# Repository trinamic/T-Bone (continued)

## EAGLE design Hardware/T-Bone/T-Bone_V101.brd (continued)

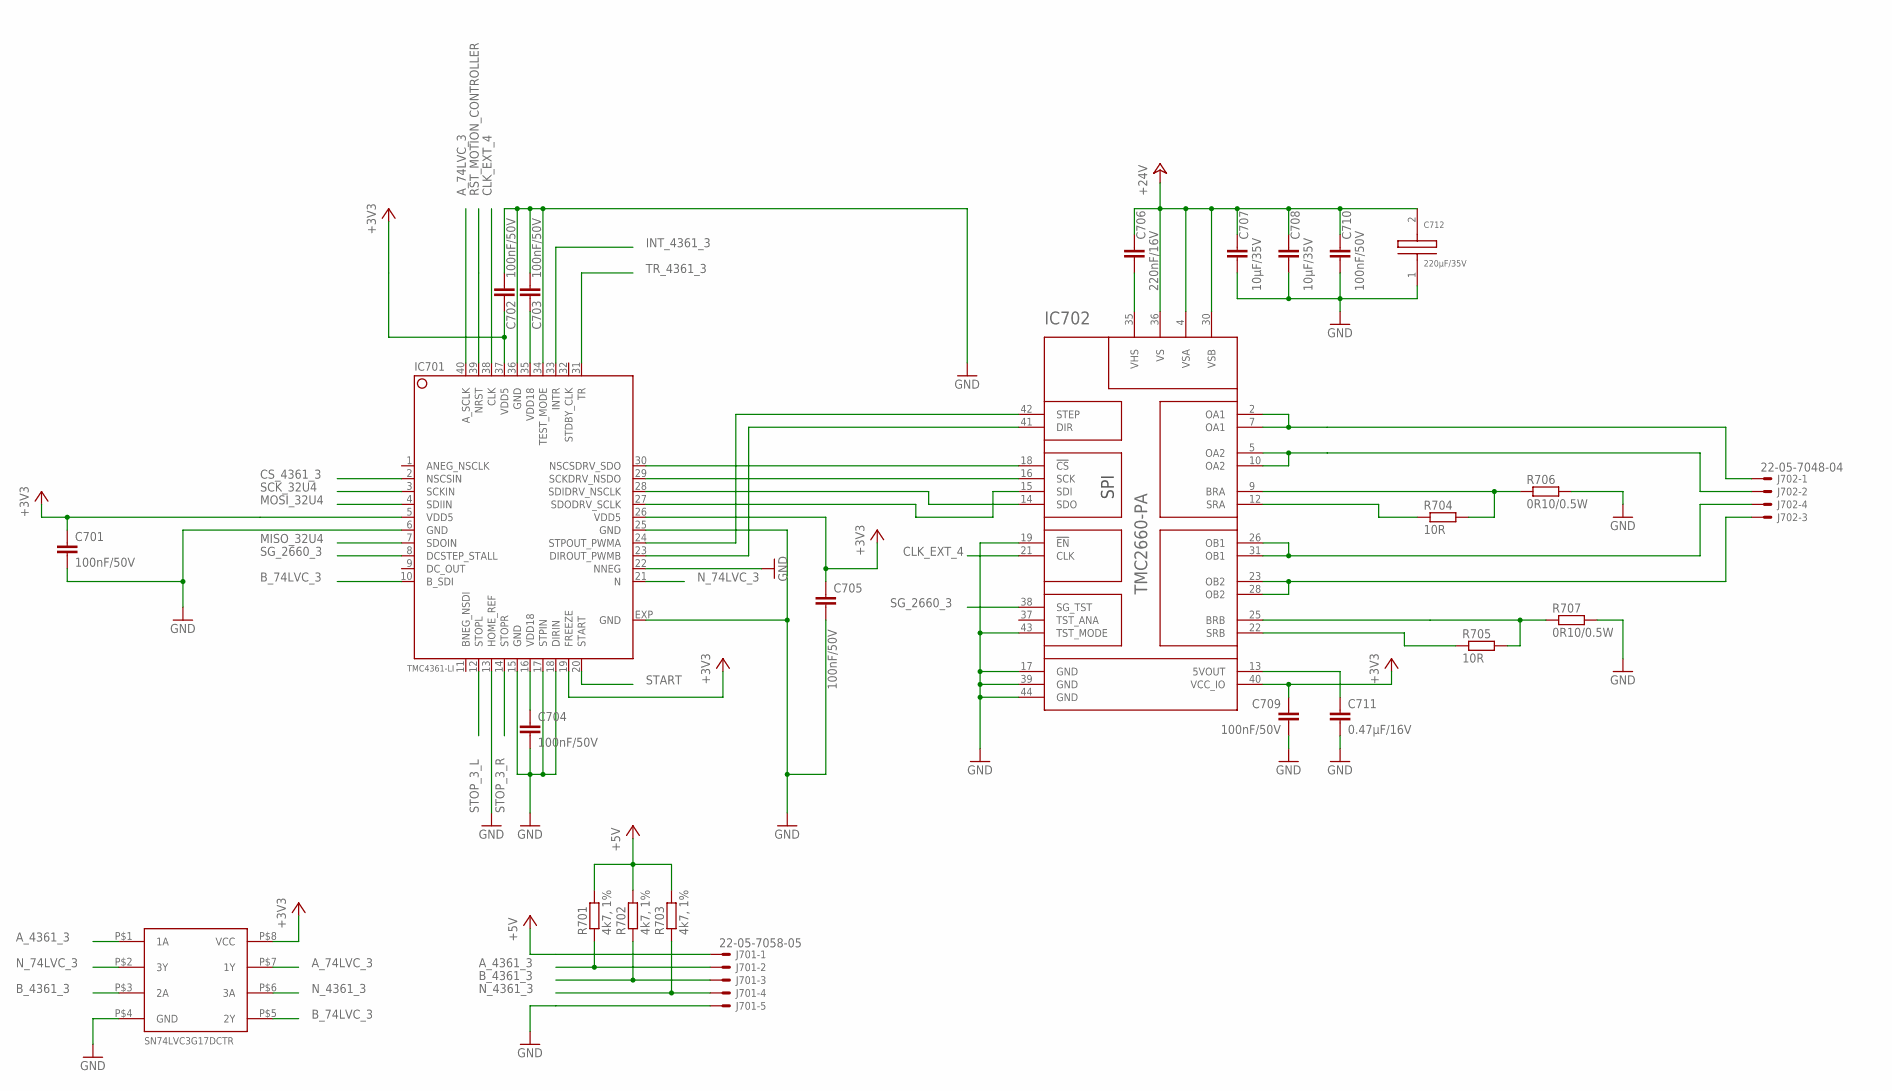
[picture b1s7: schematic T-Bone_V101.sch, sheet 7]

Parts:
C701, C702, C703, C704, C705, C709, C710: 100nF/50V; C0603K
C706: 220nF/16V; C0603K
C707, C708: 10µF/35V; C1210K
C711: 0.47µF/16V; C0603K
C712: 220µF/35V; F
IC701: TMC4361-LI; QFN40L
IC702: TMC2660-PA; PQFP44_WITH_PADS
J701: 22-05-7058-05; 7395-05
J702: 22-05-7048-04; 7395-04
R701, R702, R703: 4k7, 1%; R0603
R704, R705: 10R; R0603
R706, R707: 0R10/0.5W; R1206
U$701: SN74LVC3G17-SM8

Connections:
+3V3: C701.1, C702.2, C705.1, C709.1, IC701.5 (VDD5), IC701.19 (FREEZE), IC701.26 (VDD5), IC701.37 (VDD5), IC702.40 (VCC_IO), U$701.P$8 (VCC); also elsewhere on the board
+5V: J701.1, R701.2, R702.2, R703.2; also elsewhere on the board
+24V: C706.1, C707.1, C708.1, C710.1, C712.2, IC702.4 (VSA), IC702.30 (VSB), IC702.36 (VS); also elsewhere on the board
A_74LVC_3: IC701.40 (A_SCLK), U$701.P$7 (1Y)
A_4361_3: J701.2, R701.1, U$701.P$1 (1A)
B_74LVC_3: IC701.10 (B_SDI), U$701.P$5 (2Y)
B_4361_3: J701.3, R702.1, U$701.P$3 (2A)
CLK_EXT_4: IC701.38 (CLK), IC702.21 (CLK); also elsewhere on the board
CS_4361_3: IC701.2 (NSCSIN); also elsewhere on the board
GND: C701.2, C702.1, C703.1, C704.2, C705.2, C707.2, C708.2, C709.2, C710.2, C711.2, C712.1, IC701.6 (GND), IC701.13 (HOME_REF), IC701.15 (GND), IC701.17 (STPIN), IC701.18 (DIRIN), IC701.22 (NNEG), IC701.25 (GND), IC701.34 (TEST_MODE), IC701.36 (GND), IC701.EXP (GND), IC702.17 (GND), IC702.19 (!EN), IC702.39 (GND), IC702.43 (TST_MODE), IC702.44 (GND), J701.5, R706.2, R707.2, U$701.P$4 (GND); also elsewhere on the board
IC702_OA1: IC702.2 (OA1), IC702.7 (OA1), J702.1
IC702_OA2: IC702.5 (OA2), IC702.10 (OA2), J702.2
IC702_OB1: IC702.26 (OB1), IC702.31 (OB1), J702.4
IC702_OB2: IC702.23 (OB2), IC702.28 (OB2), J702.3
INT_4361_3: IC701.33 (INTR); also elsewhere on the board
MISO_32U4: IC701.7 (SDOIN); also elsewhere on the board
MOSI_32U4: IC701.4 (SDIIN); also elsewhere on the board
unnamed: IC701.24 (STPOUT_PWMA), IC702.42 (STEP)
unnamed: IC701.23 (DIROUT_PWMB), IC702.41 (DIR)
unnamed: IC701.28 (SDIDRV_NSCLK), IC702.14 (SDO)
unnamed: IC701.27 (SDODRV_SCLK), IC702.15 (SDI)
unnamed: C711.1, IC702.13 (5VOUT)
unnamed: IC702.9 (BRA), R704.2, R706.1
unnamed: IC702.12 (SRA), R704.1
unnamed: IC701.29 (SCKDRV_NSDO), IC702.16 (SCK)
unnamed: IC701.30 (NSCSDRV_SDO), IC702.18 (!CS)
unnamed: C706.2, IC702.35 (VHS)
unnamed: IC702.25 (BRB), R705.2, R707.1
unnamed: IC702.22 (SRB), R705.1
unnamed: C703.2, IC701.35 (VDD18)
unnamed: C704.1, IC701.16 (VDD18)
N_74LVC_3: IC701.21 (N), U$701.P$2 (3Y)
N_4361_3: J701.4, R703.1, U$701.P$6 (3A)
RST_MOTION_CONTROLLER: IC701.39 (NRST); also elsewhere on the board
SCK_32U4: IC701.3 (SCKIN); also elsewhere on the board
SG_2660_3: IC701.8 (DCSTEP_STALL), IC702.38 (SG_TST)
START: IC701.20 (START); also elsewhere on the board
STOP_3_L: IC701.12 (STOPL); also elsewhere on the board
STOP_3_R: IC701.14 (STOPR); also elsewhere on the board
TR_4361_3: IC701.31 (TR); also elsewhere on the board

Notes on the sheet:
SN74LVC3G17DCTR

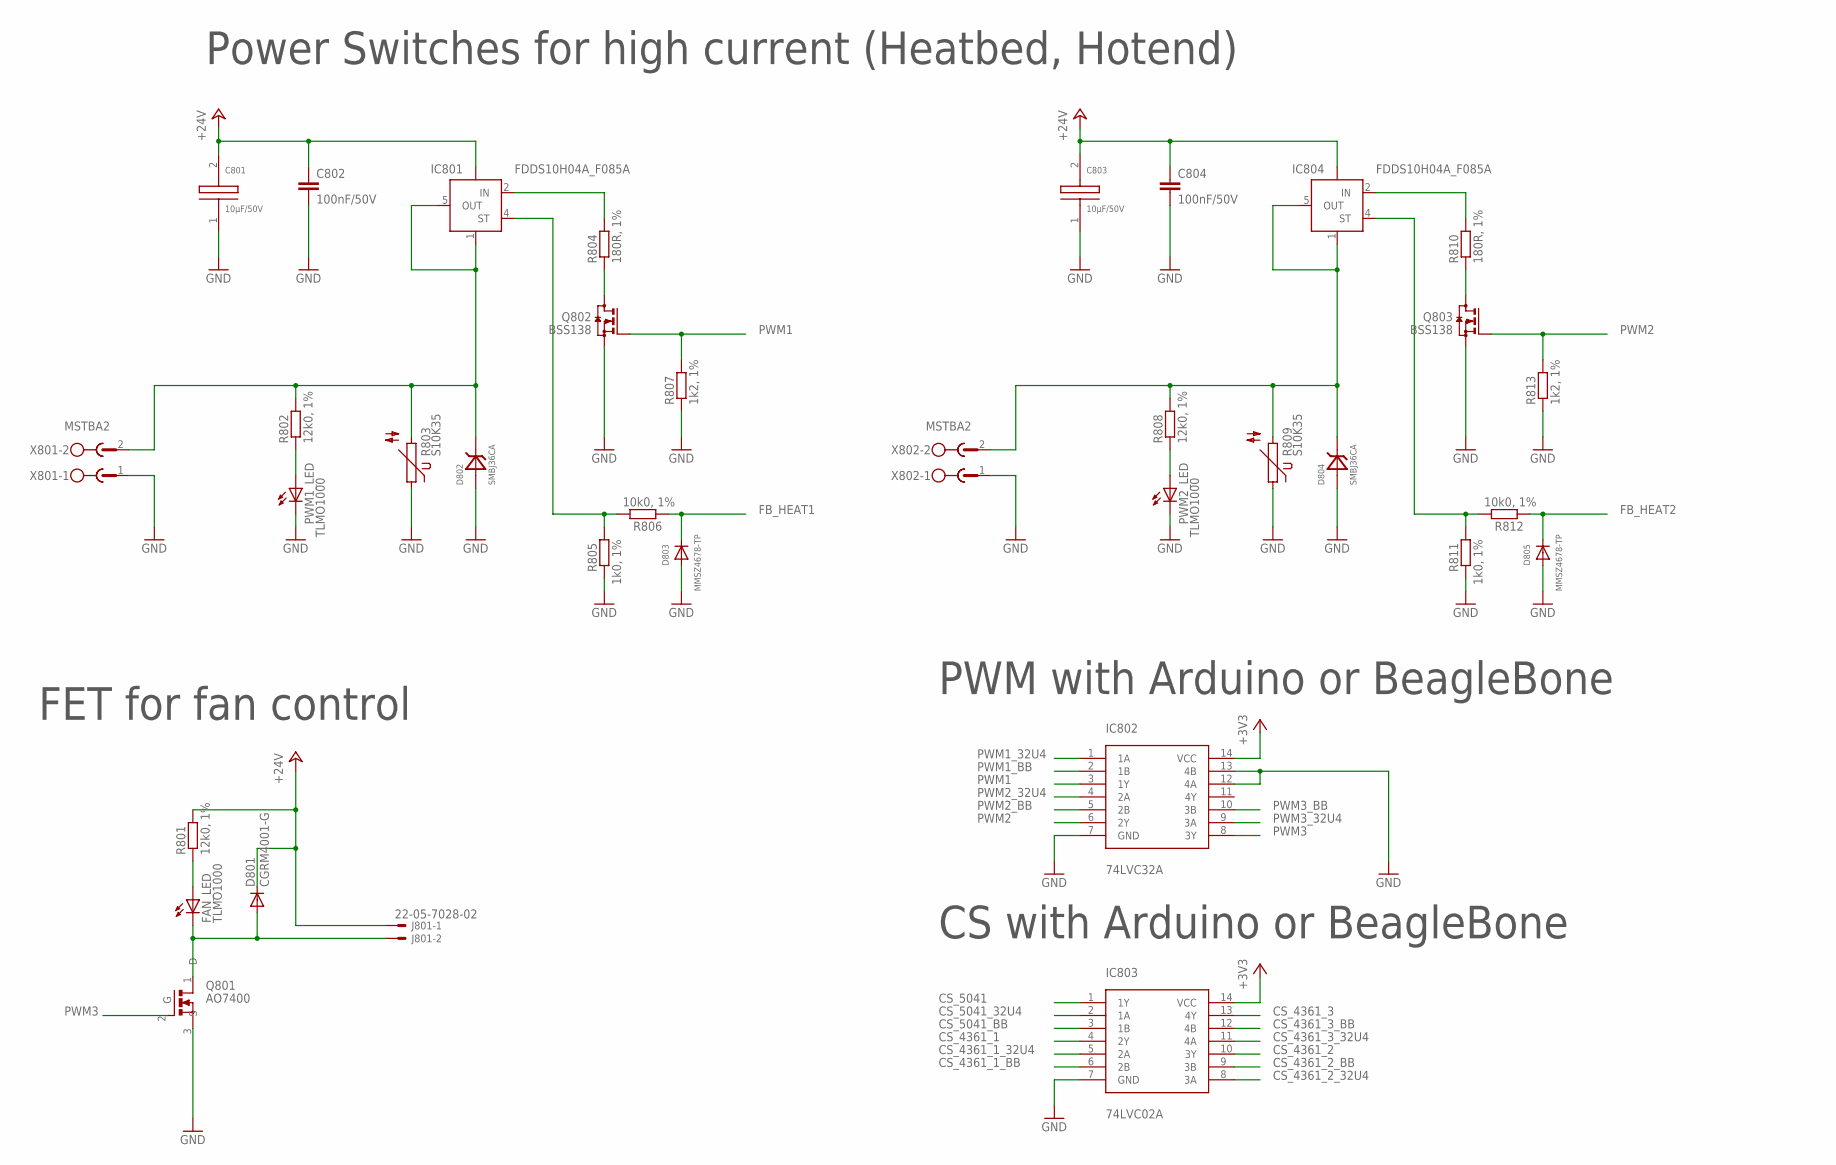
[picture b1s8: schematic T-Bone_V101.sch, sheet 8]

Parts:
C801, C803: 10µF/50V; D8
C802, C804: 100nF/50V; C0805K
D801: CGRM4001-G; SOD-123_MINI-SMA
D802, D804: SMBJ36CA; SMB
D803, D805: MMSZ4678-TP; SOD-123
FAN_LED: TLMO1000; CHIP-LED0603
IC801, IC804: FDDS10H04A_F085A; TO252-5-11
IC802: 74LVC32A; 14-VFQFN
IC803: 74LVC02A; 14-VFQFN
J801: 22-05-7028-02; 7395-02
PWM1_LED, PWM2_LED: TLMO1000; CHIP-LED0603
Q801: AO7400; SOT323
Q802, Q803: BSS138; SOT23
R801, R802, R808: 12k0, 1%; R0603
R803, R809: S10K35; S10K40
R804, R810: 180R, 1%; R0603
R805, R811: 1k0, 1%; R0603
R806, R812: 10k0, 1%; R0603
R807, R813: 1k2, 1%; R0603
X801, X802: MSTBA2

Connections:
+3V3: IC802.14 (VCC), IC803.14 (VCC); also elsewhere on the board
+24V: C801.2, C802.1, C803.2, C804.1, D801.C, IC801.TAB (VBB), IC804.TAB (VBB), J801.1, R801.2; also elsewhere on the board
CS_4361_1: IC803.4 (2Y); also elsewhere on the board
CS_4361_1_32U4: IC803.5 (2A); also elsewhere on the board
CS_4361_1_BB: IC803.6 (2B); also elsewhere on the board
CS_4361_2: IC803.10 (3Y); also elsewhere on the board
CS_4361_2_32U4: IC803.8 (3A); also elsewhere on the board
CS_4361_2_BB: IC803.9 (3B); also elsewhere on the board
CS_4361_3: IC803.13 (4Y); also elsewhere on the board
CS_4361_3_32U4: IC803.11 (4A); also elsewhere on the board
CS_4361_3_BB: IC803.12 (4B); also elsewhere on the board
CS_5041: IC803.1 (1Y); also elsewhere on the board
CS_5041_32U4: IC803.2 (1A); also elsewhere on the board
CS_5041_BB: IC803.3 (1B); also elsewhere on the board
FB_HEAT1: D803.C, R806.1; also elsewhere on the board
FB_HEAT2: D805.C, R812.1; also elsewhere on the board
GND: C801.1, C802.2, C803.1, C804.2, D802.A, D803.A, D804.A, D805.A, IC802.7 (GND), IC802.12 (4A), IC802.13 (4B), IC803.7 (GND), PWM1_LED.C, PWM2_LED.C, Q801.3 (S), Q802.2 (S), Q803.2 (S), R803.1, R805.1, R807.1, R809.1, R811.1, R813.1, X801.1, X802.1; also elsewhere on the board
HEAT1: D802.C, IC801.1 (GND), IC801.5 (OUT), R802.2, R803.2, X801.2
HEAT2: D804.C, IC804.1 (GND), IC804.5 (OUT), R808.2, R809.2, X802.2
unnamed: Q802.3 (D), R804.1
unnamed: D801.A, FAN_LED.C, J801.2, Q801.1 (D)
unnamed: FAN_LED.A, R801.1
unnamed: PWM1_LED.A, R802.1
unnamed: PWM2_LED.A, R808.1
unnamed: IC801.4 (ST), R805.2, R806.2
unnamed: IC801.2 (IN), R804.2
unnamed: Q803.3 (D), R810.1
unnamed: IC804.4 (ST), R811.2, R812.2
unnamed: IC804.2 (IN), R810.2
PWM1: IC802.3 (1Y), Q802.1 (G), R807.2
PWM1_32U4: IC802.1 (1A); also elsewhere on the board
PWM1_BB: IC802.2 (1B); also elsewhere on the board
PWM2: IC802.6 (2Y), Q803.1 (G), R813.2
PWM2_32U4: IC802.4 (2A); also elsewhere on the board
PWM2_BB: IC802.5 (2B); also elsewhere on the board
PWM3: IC802.8 (3Y), Q801.2 (G)
PWM3_32U4: IC802.9 (3A); also elsewhere on the board
PWM3_BB: IC802.10 (3B); also elsewhere on the board

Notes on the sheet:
CS with Arduino or BeagleBone
PWM with Arduino or BeagleBone
FET for fan control
Power Switches for high current (Heatbed, Hotend)

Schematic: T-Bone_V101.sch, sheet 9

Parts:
END1L_LED, END1R_LED, END2L_LED, END2R_LED, END3L_LED, END3R_LED, END4L_LED, END4R_LED, END5L_LED, END5R_LED: LEDCHIP-LED0603; CHIP-LED0603
J450, J460, J470, J480, J550, J560, J650, J660, J750, J760: 22-05-7038-03; 7395-03
R450, R451, R460, R461, R470, R471, R480, R481, R550, R551, R560, R561, R650, R651, R660, R661, R750, R751, R760, R761: 4k7, 1%; R0402
R452, R462, R472, R482, R552, R562, R652, R662, R752, R762: 10k; R0402
SJ450, SJ460, SJ470, SJ480, SJ550, SJ560, SJ650, SJ660, SJ750, SJ760: SJ2W; SJ_2

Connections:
+3V3: J450.1, J460.1, J470.1, J480.1, J550.1, J560.1, J650.1, J660.1, J750.1, J760.1, R451.2, R461.2, R471.2, R481.2, R551.2, R561.2, R651.2, R661.2, R751.2, R761.2; also elsewhere on the board
GND: J450.3, J460.3, J470.3, J480.3, J550.3, J560.3, J650.3, J660.3, J750.3, J760.3, R450.1, R452.1, R460.1, R462.1, R470.1, R472.1, R480.1, R482.1, R550.1, R552.1, R560.1, R562.1, R650.1, R652.1, R660.1, R662.1, R750.1, R752.1, R760.1, R762.1; also elsewhere on the board
unnamed: R471.1, SJ470.1
unnamed: END1L_LED.C, R552.2
unnamed: END2L_LED.C, R652.2
unnamed: R470.2, SJ470.3
unnamed: END4L_LED.C, R452.2
unnamed: END3L_LED.C, R752.2
unnamed: END1R_LED.C, R562.2
unnamed: END2R_LED.C, R662.2
unnamed: END4R_LED.C, R462.2
unnamed: END3R_LED.C, R762.2
unnamed: END5L_LED.C, R472.2
unnamed: R481.1, SJ480.1
unnamed: R480.2, SJ480.3
unnamed: END5R_LED.C, R482.2
unnamed: R650.2, SJ650.3
unnamed: R651.1, SJ650.1
unnamed: R451.1, SJ450.1
unnamed: R550.2, SJ550.3
unnamed: R551.1, SJ550.1
unnamed: R450.2, SJ450.3
unnamed: R560.2, SJ560.3
unnamed: R561.1, SJ560.1
unnamed: R661.1, SJ660.1
unnamed: R660.2, SJ660.3
unnamed: R460.2, SJ460.3
unnamed: R461.1, SJ460.1
unnamed: R751.1, SJ750.1
unnamed: R750.2, SJ750.3
unnamed: R761.1, SJ760.1
unnamed: R760.2, SJ760.3
STOP_1_L: END1L_LED.A, J550.2, SJ550.2; also elsewhere on the board
STOP_1_R: END1R_LED.A, J560.2, SJ560.2; also elsewhere on the board
STOP_2_L: END2L_LED.A, J650.2, SJ650.2; also elsewhere on the board
STOP_2_R: END2R_LED.A, J660.2, SJ660.2; also elsewhere on the board
STOP_3_L: END3L_LED.A, J750.2, SJ750.2; also elsewhere on the board
STOP_3_R: END3R_LED.A, J760.2, SJ760.2; also elsewhere on the board
STOP_4_L: END4L_LED.A, J450.2, SJ450.2; also elsewhere on the board
STOP_4_R: END4R_LED.A, J460.2, SJ460.2; also elsewhere on the board
STOP_5_L: END5L_LED.A, J470.2, SJ470.2; also elsewhere on the board
STOP_5_R: END5R_LED.A, J480.2, SJ480.2; also elsewhere on the board

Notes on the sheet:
Connectors for Endstops (Pullup/-down optional)

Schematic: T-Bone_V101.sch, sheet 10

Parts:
C901, C902, C903, C904, C905, C906: 470nF/50V; C0402K
J902, J904, J907: 22-05-7028-02; 7395-02
R901, R903, R905: 4k7, 1%; R0402
R902, R904, R906: 6k8, 1%; R0402

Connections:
1V8_ADC_BB: R901.2, R903.2, R905.2; also elsewhere on the board
GND: C901.2, C902.2, C903.2, C904.2, C905.2, C906.2, J902.2, J904.2, J907.2; also elsewhere on the board
unnamed: C901.1, J902.1, R901.1, R902.1
unnamed: C903.1, J904.1, R903.1, R904.1
unnamed: C905.1, J907.1, R905.1, R906.1
TEMP1: C902.1, R902.2; also elsewhere on the board
TEMP2: C904.1, R904.2; also elsewhere on the board
TEMP3: C906.1, R906.2; also elsewhere on the board

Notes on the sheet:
Connectors for Thermistors

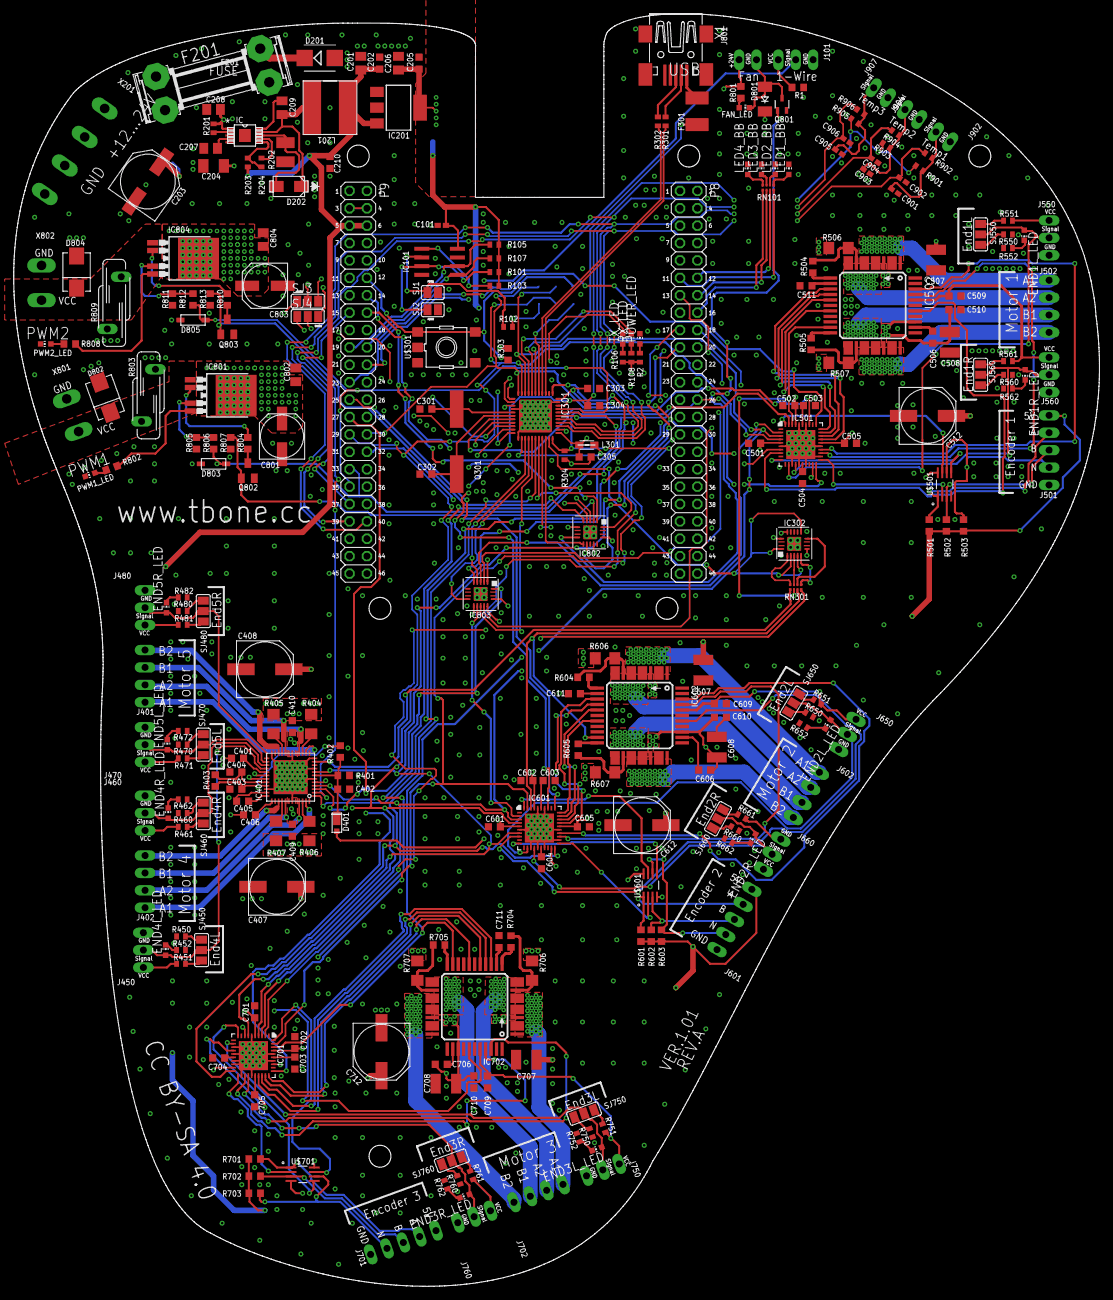
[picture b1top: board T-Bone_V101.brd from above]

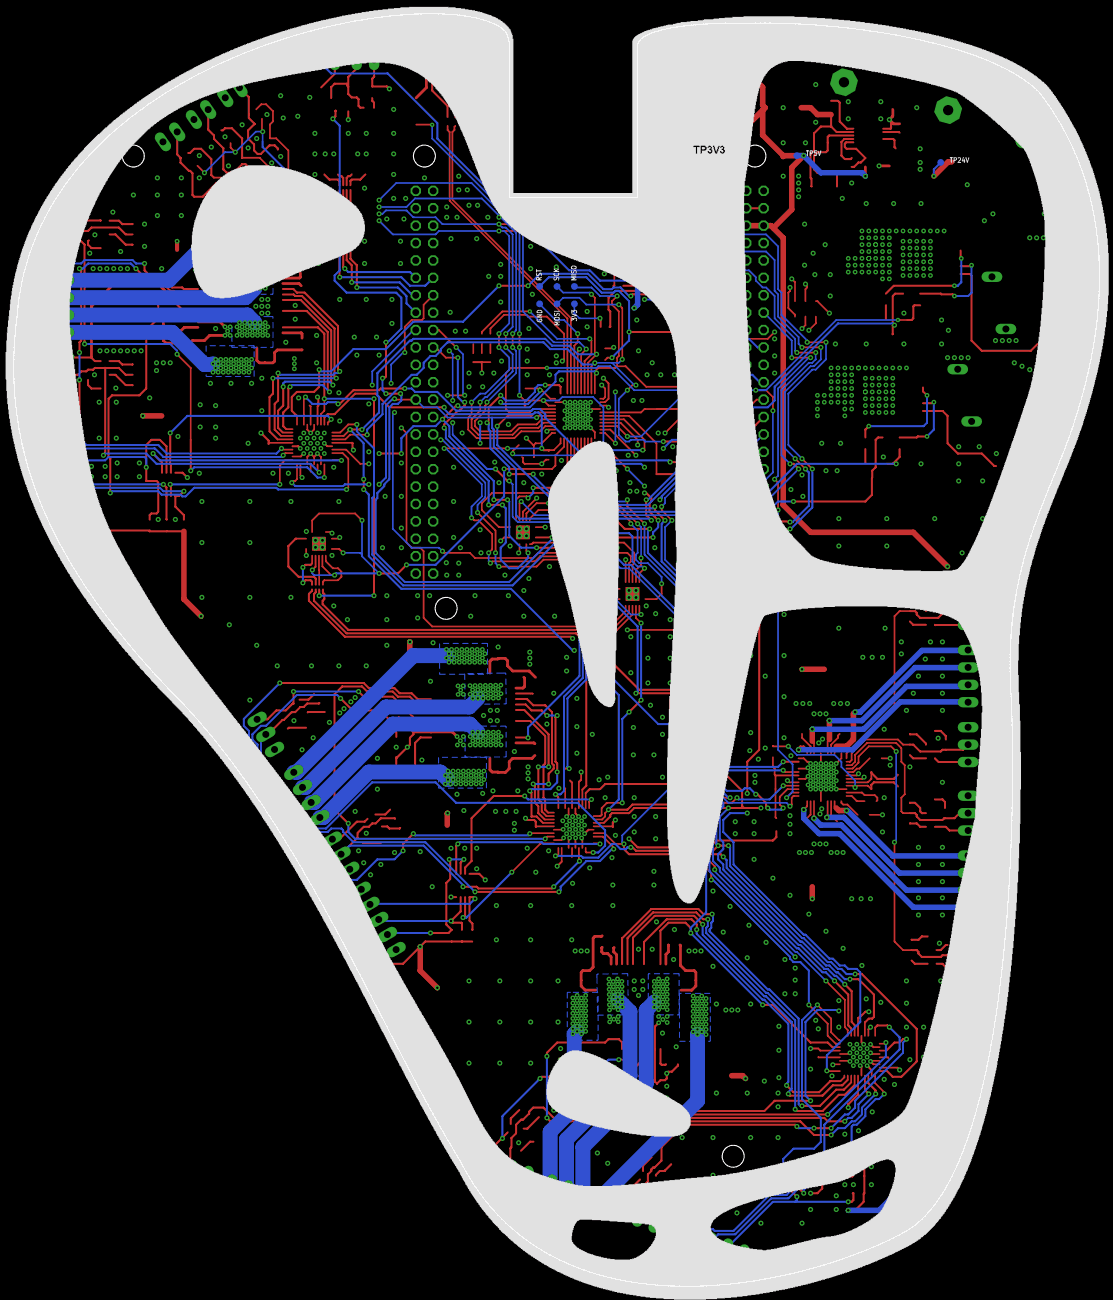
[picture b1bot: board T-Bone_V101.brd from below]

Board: 4 copper layers, 158.5 x 185.8 mm, 277 parts (9 on the bottom side), 244 nets.

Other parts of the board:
U$1: T-BONE_SILK_EXT_WITH_3V3

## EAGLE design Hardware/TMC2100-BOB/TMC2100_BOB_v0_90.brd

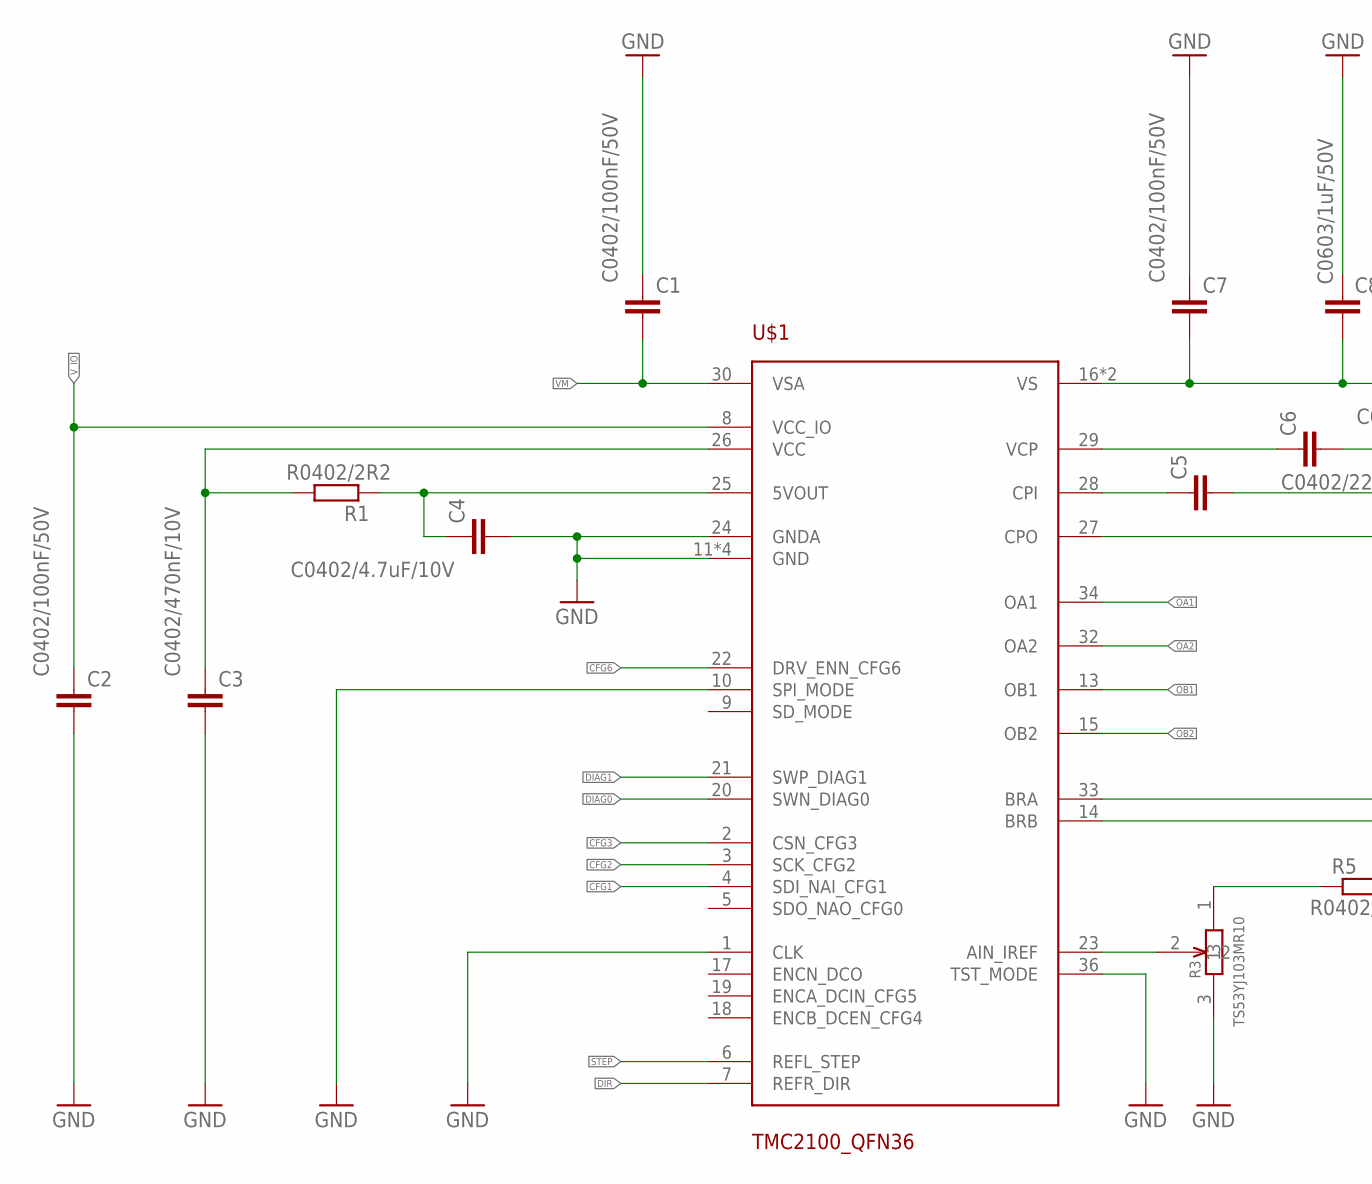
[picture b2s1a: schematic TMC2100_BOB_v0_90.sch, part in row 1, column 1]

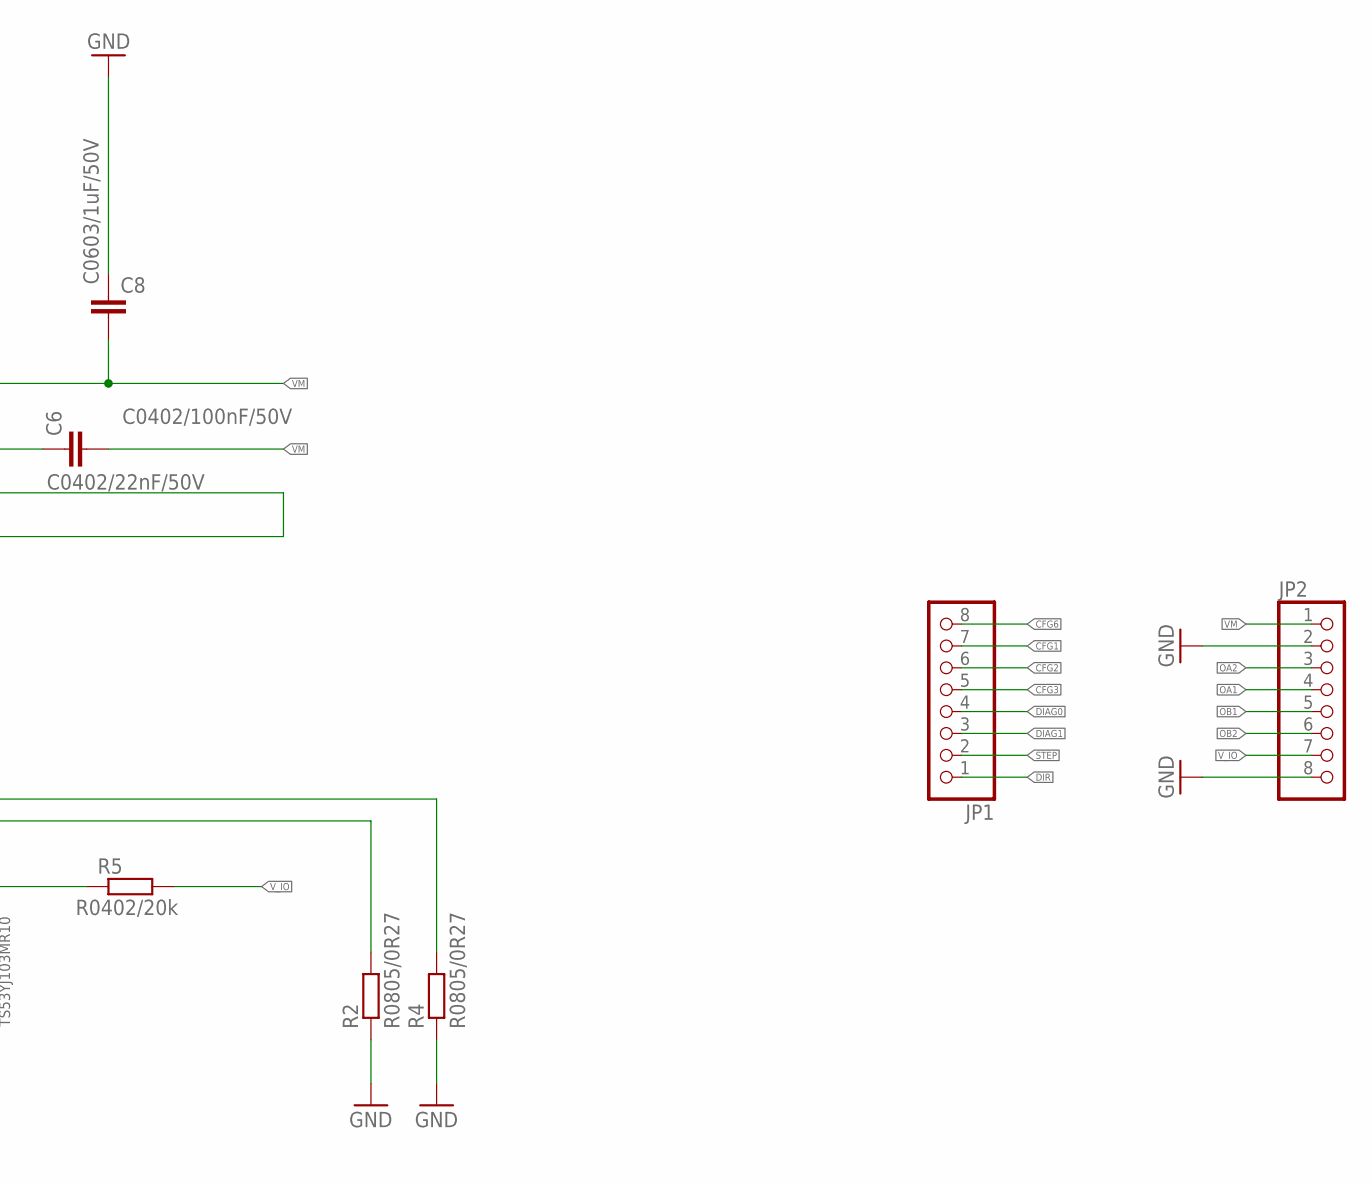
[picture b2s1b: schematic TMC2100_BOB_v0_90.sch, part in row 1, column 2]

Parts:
C1, C2, C6, C7: C0402/100nF/50V; C0402
C3: C0402/470nF/10V; C0402
C4: C0402/4.7uF/10V; C0402
C5: C0402/22nF/50V; C0402
C8: C0603/1uF/50V; C0603
JP1, JP2: PINHD-1X08_2.54-S; 1X08-S
R1: R0402/2R2; R0402
R2, R4: R0805/0R27; M0805
R3: TS53YJ103MR10; TS53YJ
R5: R0402/20k; R0402
U$1: TMC2100_QFN36; QFN36

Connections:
CFG1: JP1.7, U$1.4 (SDI_NAI_CFG1)
CFG2: JP1.6, U$1.3 (SCK_CFG2)
CFG3: JP1.5, U$1.2 (CSN_CFG3)
CFG6: JP1.8, U$1.22 (DRV_ENN_CFG6)
DIAG0: JP1.4, U$1.20 (SWN_DIAG0)
DIAG1: JP1.3, U$1.21 (SWP_DIAG1)
DIR: JP1.1, U$1.7 (REFR_DIR)
GND: C1.1, C2.2, C3.2, C4.2, C7.1, C8.2, JP2.2, JP2.8, R2.1, R3.3, R4.1, U$1.1 (CLK), U$1.10 (SPI_MODE), U$1.11 (GND), U$1.12 (GND), U$1.24 (GNDA), U$1.35 (GND), U$1.36 (TST_MODE), U$1.GND_PAD (GND)
unnamed: C3.1, R1.2, U$1.26 (VCC)
unnamed: C4.1, R1.1, U$1.25 (5VOUT)
unnamed: C6.1, U$1.29 (VCP)
unnamed: C5.1, U$1.28 (CPI)
unnamed: R4.2, U$1.33 (BRA)
unnamed: C5.2, U$1.27 (CPO)
unnamed: R2.2, U$1.14 (BRB)
unnamed: R3.1, R5.1
unnamed: R3.2, U$1.23 (AIN_IREF)
OA1: JP2.4, U$1.34 (OA1)
OA2: JP2.3, U$1.32 (OA2)
OB1: JP2.5, U$1.13 (OB1)
OB2: JP2.6, U$1.15 (OB2)
STEP: JP1.2, U$1.6 (REFL_STEP)
VM: C1.2, C6.2, C7.2, C8.1, JP2.1, U$1.16 (VS), U$1.30 (VSA), U$1.31 (VS)
V_IO: C2.1, JP2.7, R5.2, U$1.8 (VCC_IO)

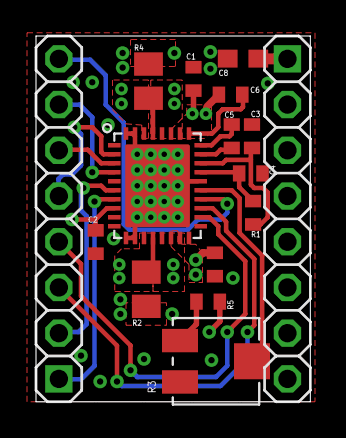
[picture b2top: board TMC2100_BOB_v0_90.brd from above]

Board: 4 copper layers, 15.2 x 20.3 mm, 16 parts (0 on the bottom side), 24 nets.

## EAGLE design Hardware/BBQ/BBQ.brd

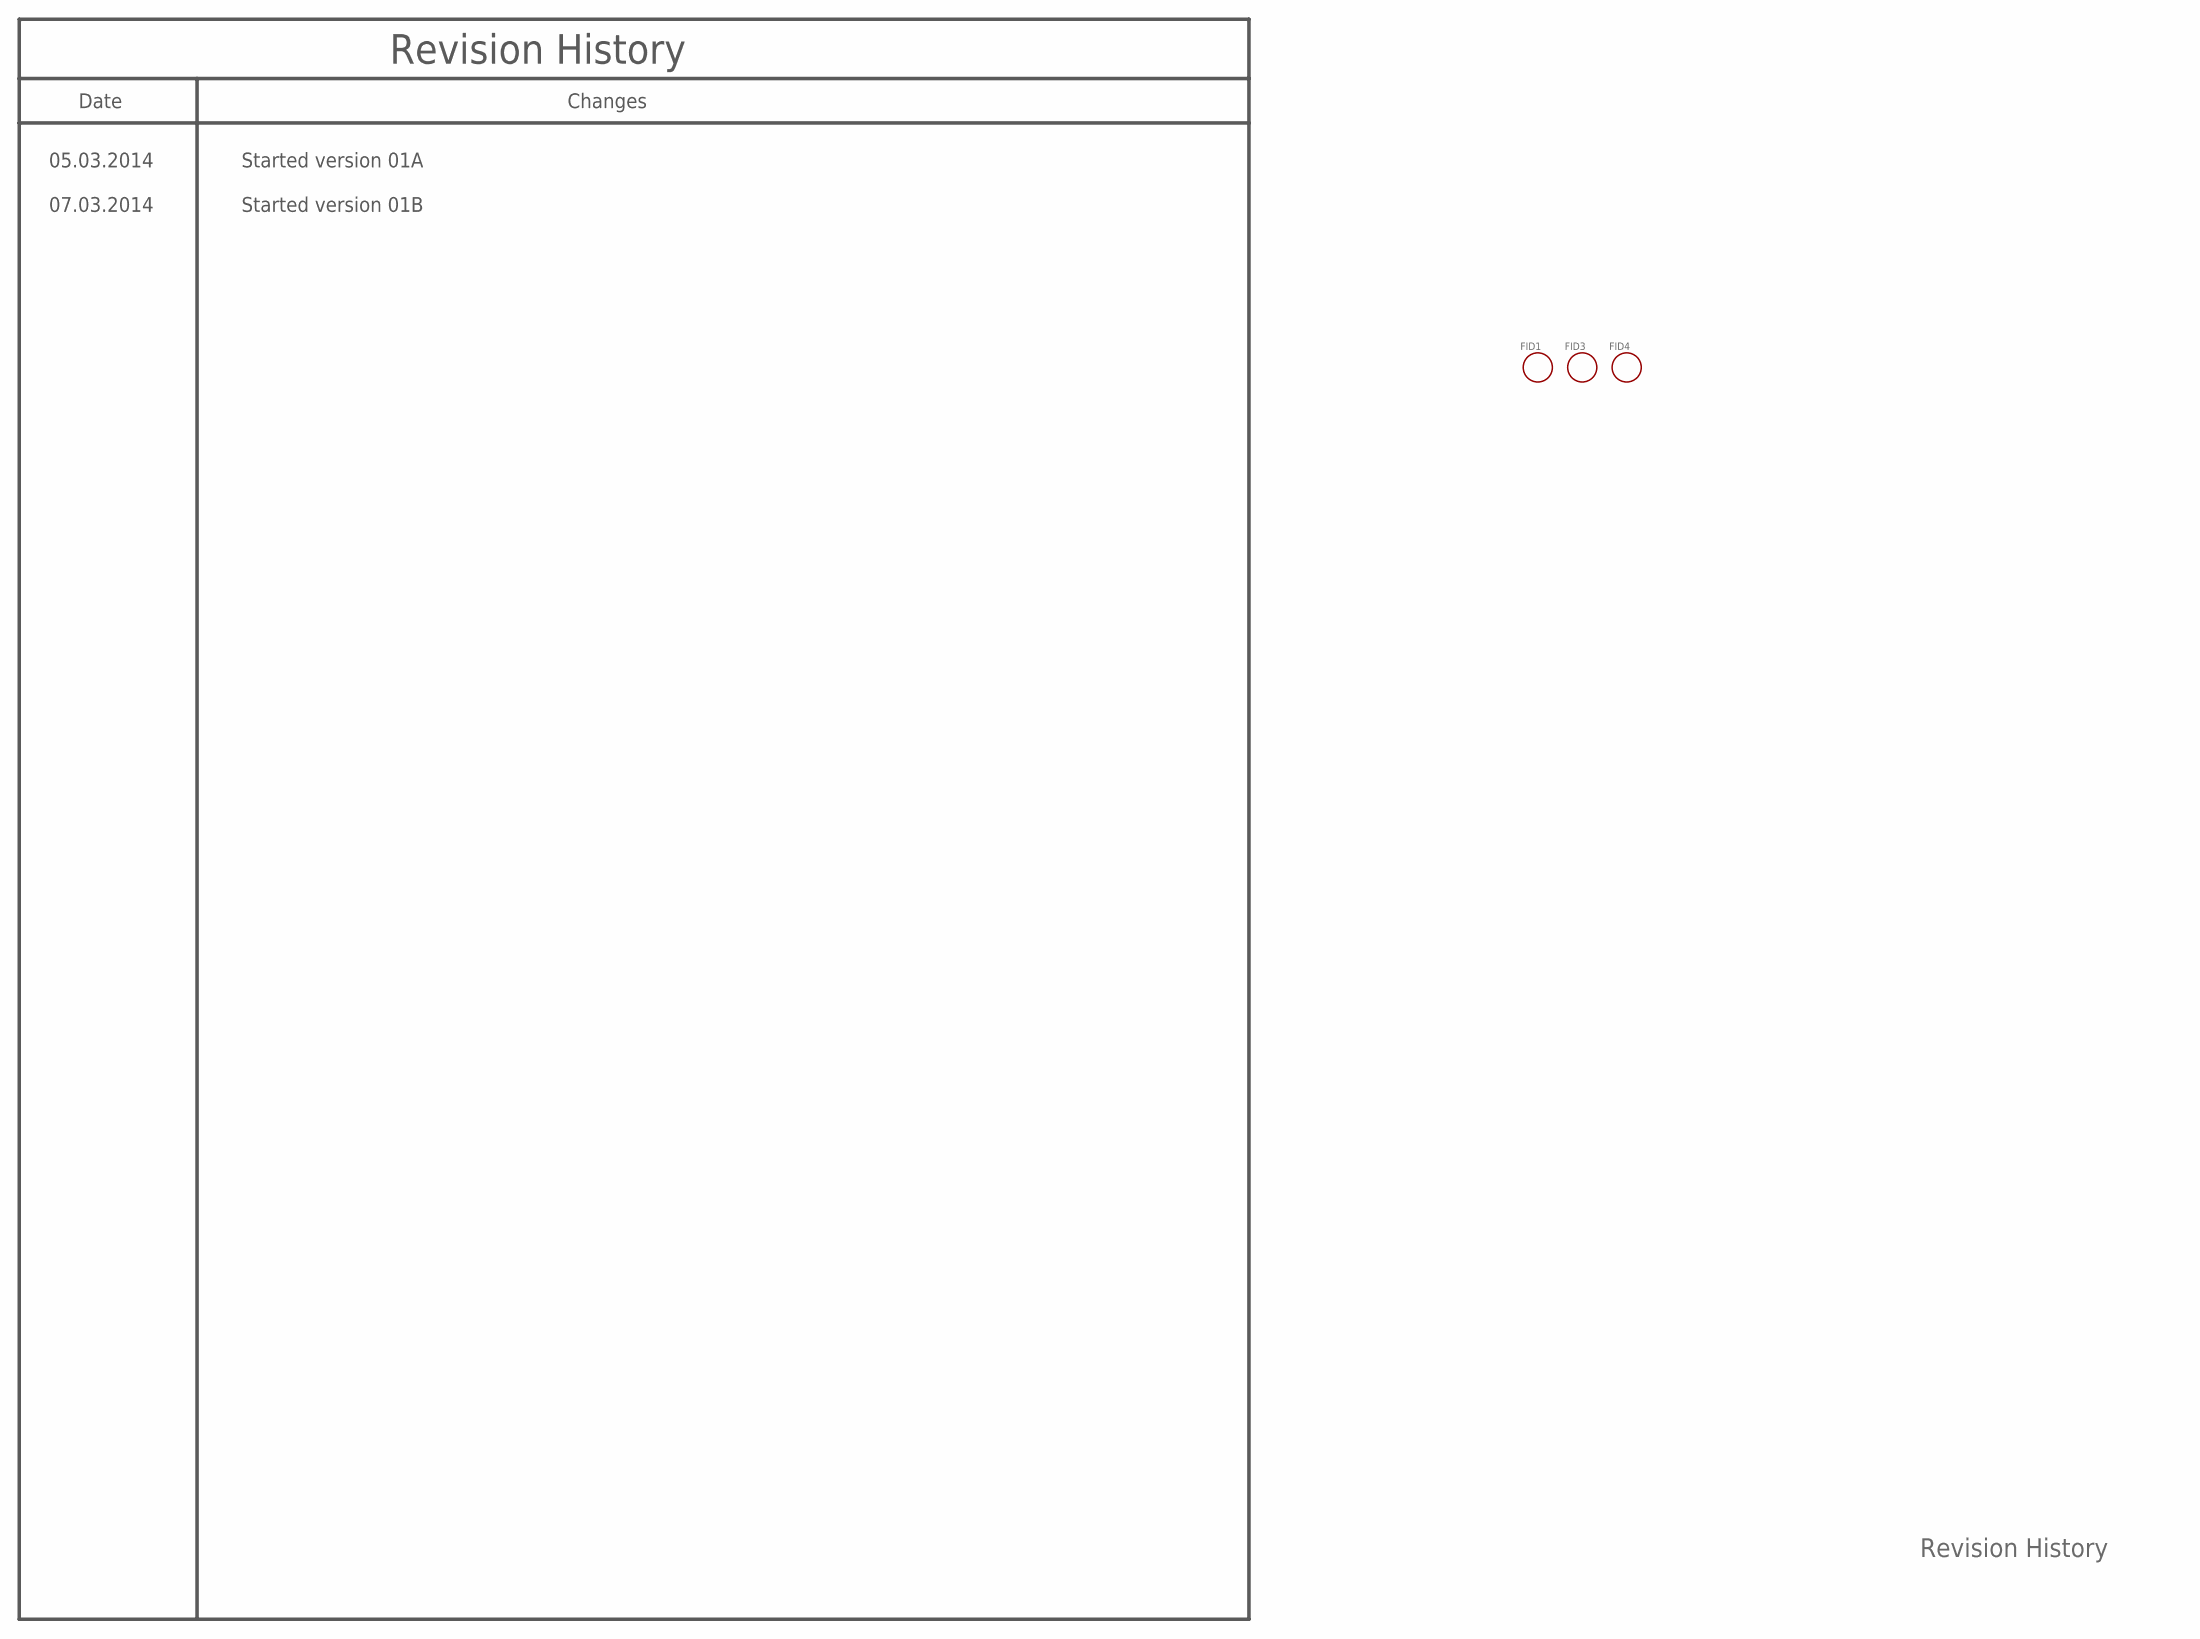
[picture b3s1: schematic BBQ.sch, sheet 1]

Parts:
FID1, FID3, FID4: FIDUCIAL

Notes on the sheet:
Revision History
Changes
Date
05.03.2014
Started version 01A
07.03.2014
Started version 01B
